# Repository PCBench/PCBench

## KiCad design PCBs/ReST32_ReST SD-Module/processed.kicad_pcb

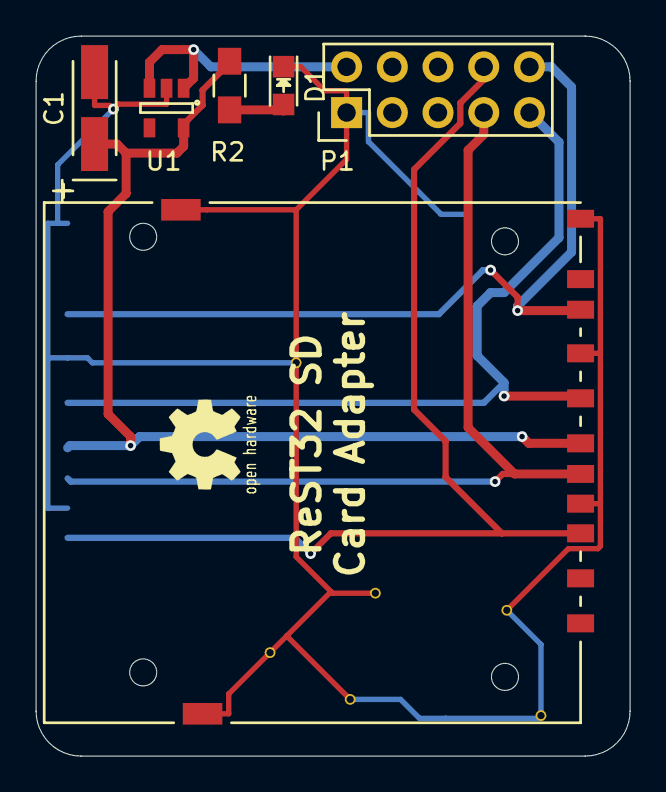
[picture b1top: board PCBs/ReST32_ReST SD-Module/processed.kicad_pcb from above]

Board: 2 copper layers, 33.0 x 40.0 mm, 7 parts (1 on the bottom side), 8 nets.

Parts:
C1: 2.2uF; TantalC_SizeA_EIA-3216_HandSoldering
CON1, CON2: uSD_Card; SD_Card_Receptacle
D1: Led_Small; LED_0805
P1: CONN_02X05; Pin_Header_Straight_2x05
R2: 1K; R_0805_HandSoldering
U1: MIC5205; SOT-23-5

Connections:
+3V3: C1.1, CON1.4, CON2.4, R2.1, U1.5
+5V: P1.2, U1.1, U1.3
/SPI-CS: CON1.2, CON2.2, P1.8
/SPI-MISO: CON1.7, CON2.7, P1.10
/SPI-MOSI: CON1.3, CON2.3, P1.7
/SPI-SCK: CON1.5, CON2.5, P1.9
GND: C1.2, CON1.6, CON1.10, CON1.11, CON1.12, CON1.13, CON2.6, CON2.10, CON2.11, CON2.12, CON2.13, D1.1, P1.1, U1.2
unnamed: D1.2, R2.2

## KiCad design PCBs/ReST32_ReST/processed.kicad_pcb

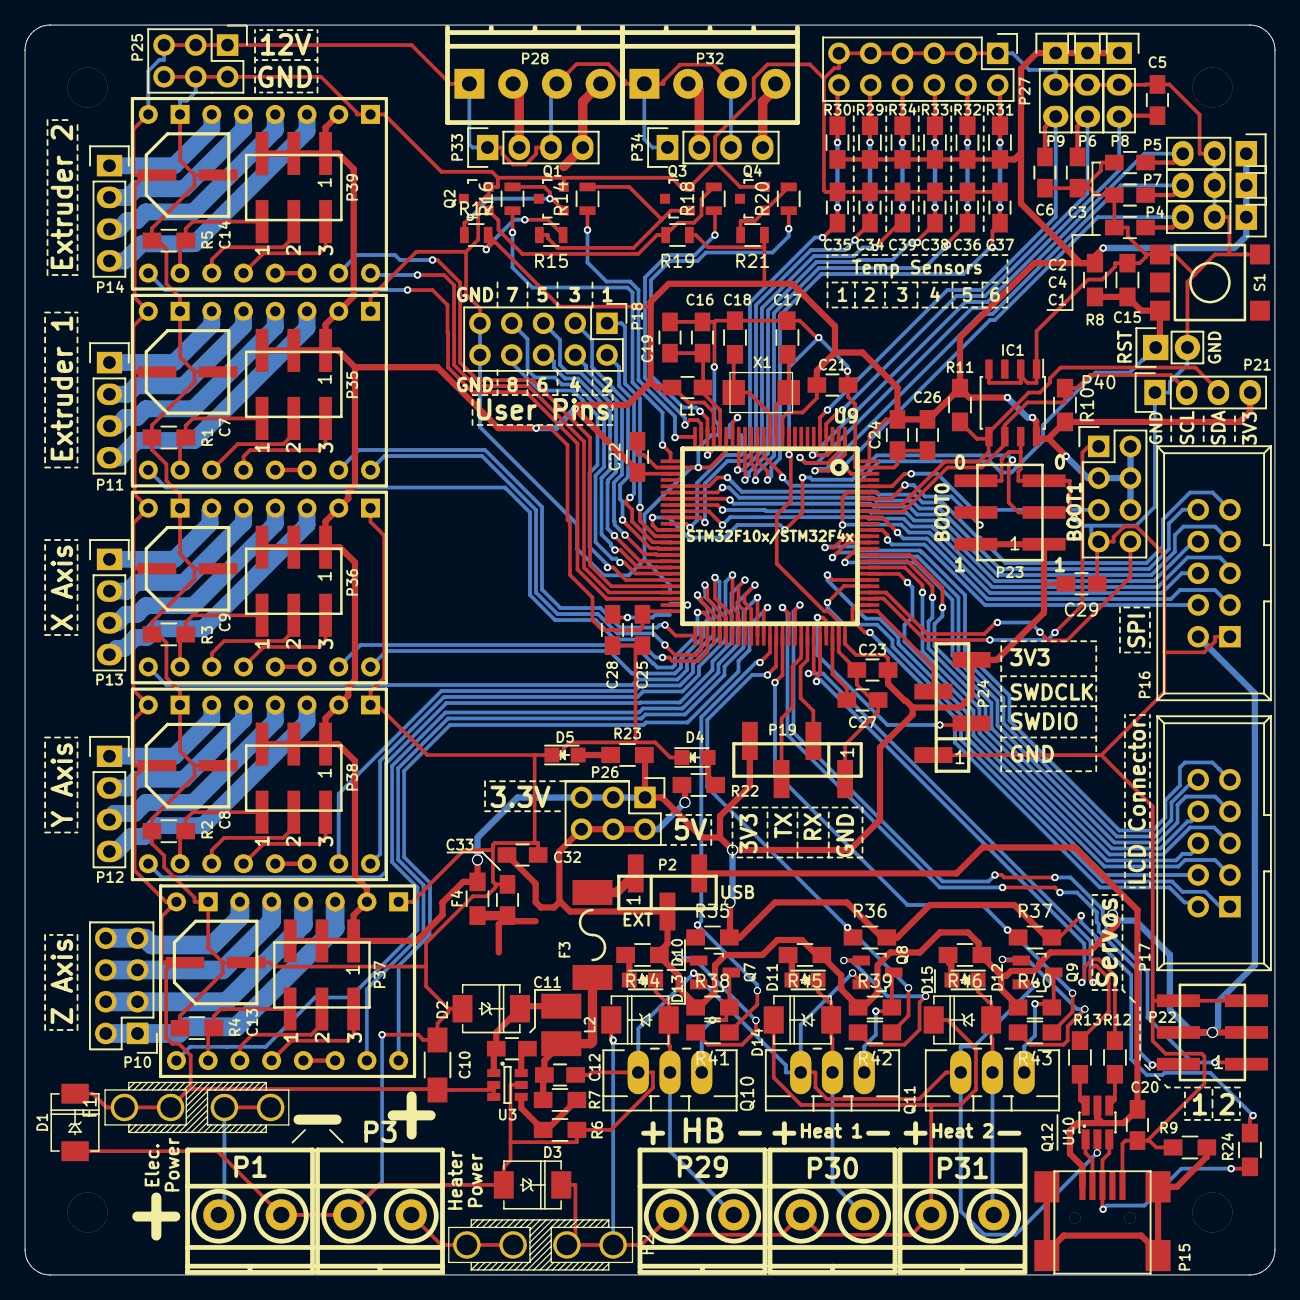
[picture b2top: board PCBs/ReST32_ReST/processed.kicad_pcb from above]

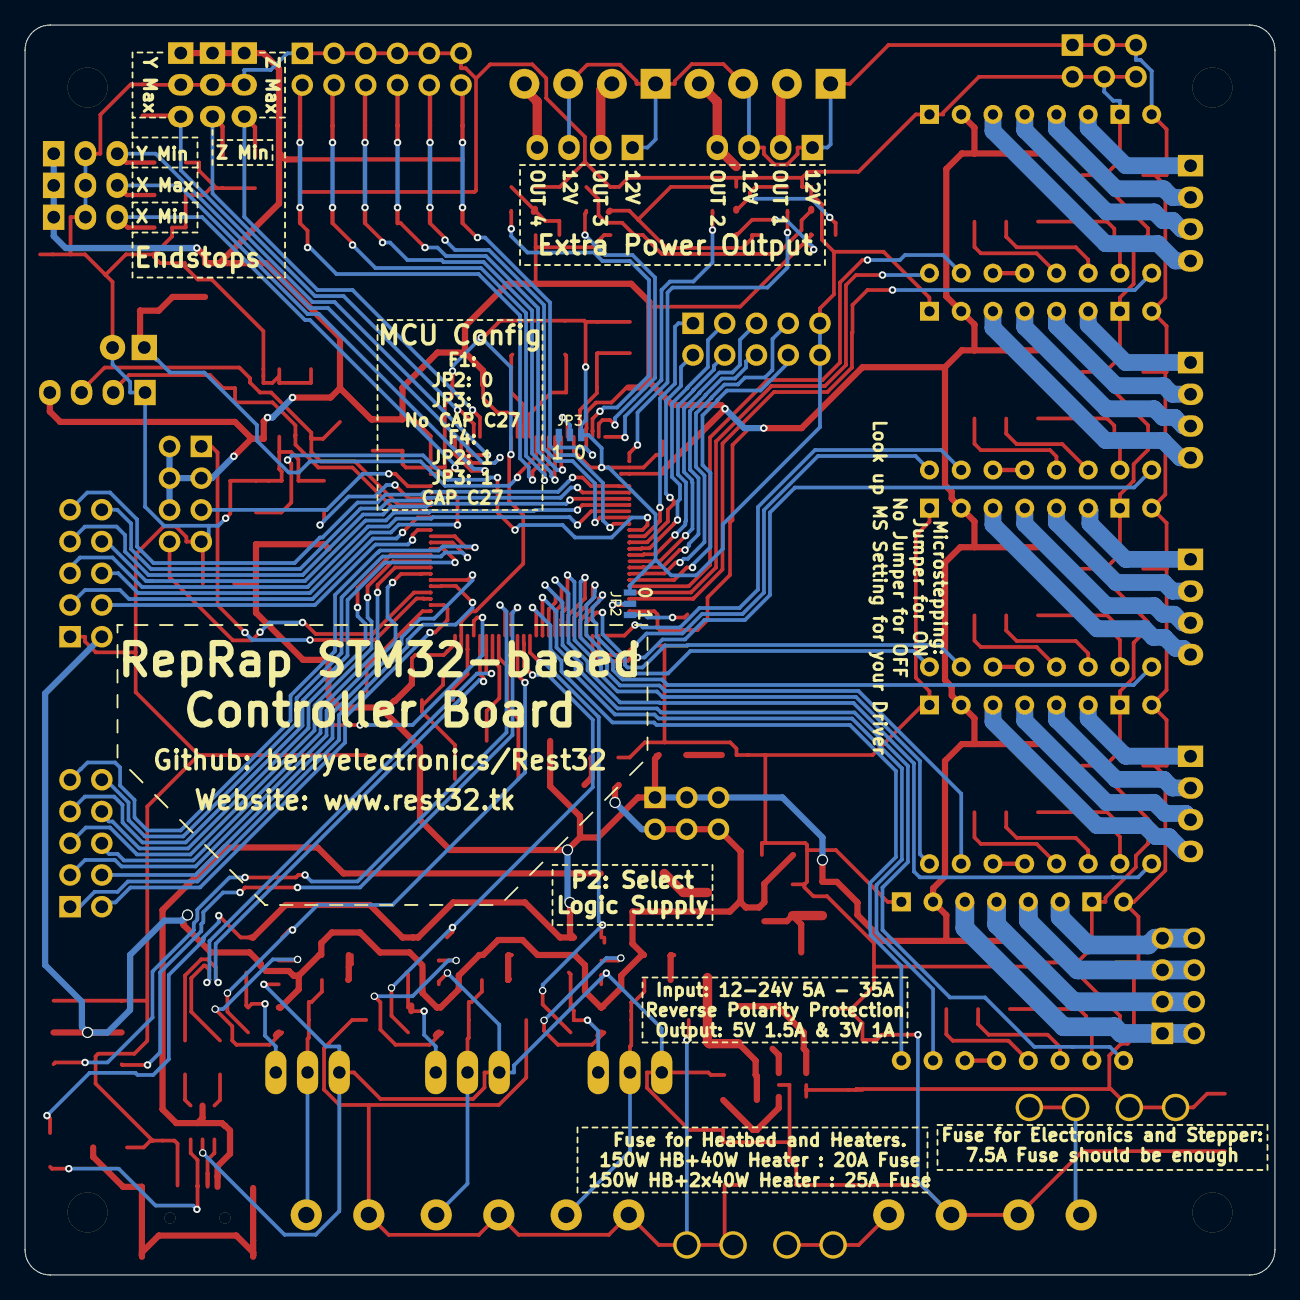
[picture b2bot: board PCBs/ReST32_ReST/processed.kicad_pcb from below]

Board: 2 copper layers, 100.0 x 100.0 mm, 159 parts (2 on the bottom side), 164 nets.

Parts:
C1, C2, C3, C4, C5, C6: 10nF; C_0805_HandSoldering
C7, C8, C9, C13, C14: 100uF; CP-PANASONIC-SMT_D8
C10: 10uF; C_1206_HandSoldering
C11: 22nF; C_0805_HandSoldering
C12, C26: 4.7uF; C_0805_HandSoldering
C15: 100nF; R_0805_HandSoldering
C16, C32, C33, C34, C35, C36, C37, C38, C39: 10uF; C_0805_HandSoldering
C17, C18: 10pF; R_0805_HandSoldering
C19, C20, C21, C22, C23, C24, C25, C29: 100nF; C_0805_HandSoldering
C27, C28: 2u2; C_0805_HandSoldering
D1, D3: 1N400x; DO-214AC.SMA
D2: B240A; DO-214AC.SMA
D4, D5, D10, D11, D12: LED; LED_0805
D13, D14, D15: D_1N400x-SMD; DO-214AC.SMA
F1, F2: F_Small; MINI-FUSE
F3: F_Small; FUSE-1812
F4: F_Small; R_0805_HandSoldering
IC1: AT24C256; SOIC-8_3.9x4.9mm_Pitch1.27mm
JP2, JP3: JUMPER3; S_JUMPER_3
L1: BEAD; C_0805_HandSoldering
L2: 4.7uH; CD32
P1, P3, P29, P30, P31: CONN_01X02; screw-5-2P
P2: CONN_01X03; bb02-hy03a
P4, P5, P6, P7, P8, P9: CONN_01X03; Pin_Header_Straight_1x03
P10, P40: CONN_02X04; Pin_Header_Straight_2x04
P11, P12, P13, P14, P21: CONN_01X04; Pin_Header_Straight_1x04
P15: USB_OTG; USB_Mini-B
P16, P17: CONN_02X05; IDC_Header_Straight_10pins
P18: CONN_02X05; Pin_Header_Straight_2x05
P19, P24: CONN_01X04; bb02-hy04a
P20: CONN_01X02; Pin_Header_Straight_1x02
P22, P23, P35, P36, P37, P38, P39: CONN_02X03; bb02-hp06
P25, P26: CONN_02X03; Pin_Header_Straight_2x03
P27: CONN_02X06; Pin_Header_Straight_2x06
P28, P32: CONN_02X02; pt_1,5-4-3,5-h
P33, P34: CONN_02X02; Pin_Header_Straight_1x04
Q1, Q2, Q3, Q4, Q7, Q8, Q9: BSS138; SOT-23
Q10, Q11, Q12: Q_AOT240L; TO-220_Neutral123_Vertical_LargePads
R1, R2, R3, R4, R5, R35, R36, R37, R38, R39, R40: 100K; R_0805_HandSoldering
R6: 28.7k; R_0805_HandSoldering
R7: 150K; R_0805_HandSoldering
R8: 10K; R_0805_HandSoldering
R9: 1M; R_0805_HandSoldering
R10, R11, R29, R30, R31, R32, R33, R34: 4K7; R_0805_HandSoldering
R12, R13, R41, R42, R43: 22R; R_0805_HandSoldering
R14, R16, R18, R20: 22R; R_0805
R15, R17, R19, R21: 100K; R_0805
R22, R23, R44, R45, R46: 1K; R_0805_HandSoldering
R24: 1K5; R_0805_HandSoldering
S1: SW_DIP_x2; SMD-BUTTON-6MM
U2, U5, U6, U7, U8: POLOLU_A4988; SWDIP8_.6W
U3: ACT4088; SOT-23-6
U9: STM32F10x/STM32F4x; LQFP100-14x14
U10: USBLC6-2; SOT32-6L
X1: Crystal_Small; 2P-5032

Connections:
+3V3: C21.1, C22.1, C23.1, C24.1, C25.1, C26.1, C29.2, F4.1, IC1.8, JP3.1, L1.1, P4.1, P5.1, P6.1, P7.1, P8.1, P9.1, P19.4, P21.4, P23.1, P23.2, P24.4, P26.1, P26.3, P26.5, P35.1, P35.3, P35.5, P36.1, P36.3, P36.5, P37.1, P37.3, P37.5, P38.1, P38.3, P38.5, P39.1, P39.3, P39.5, P40.2, P40.3, P40.4, P40.6, R8.2, R10.2, R11.2, R15.1, R17.2, R19.1, R21.1, R23.1, R24.2, R29.2, R30.2, R31.2, R32.2, R33.2, R34.2, R35.2, R36.2, R37.2, U2.2, U5.2, U6.2, U7.2, U8.2, U9.11, U9.22, U9.28, U9.50, U9.75, U9.100
+5V: C32.2, P2.2, P16.2, P22.3, P22.4, P26.2, P26.4, P26.6, R22.1, R38.1, R39.1, R40.1, R44.1, R45.1, R46.1
+12V: C7.1, C8.1, C9.1, C10.1, C13.1, C14.1, D1.1, F1.2, P25.1, P25.3, P25.5, P28.1, P28.3, P32.1, P32.3, P33.1, P33.3, P34.1, P34.3, U2.8, U3.2, U3.3, U5.8, U6.8, U7.8, U8.8
+12VA: D3.1, D13.1, D14.1, D15.1, F2.2, P29.1, P30.1, P31.1
/Extra Power Output/EXTRA_0_OUT: P28.2, P33.2
/Extra Power Output/EXTRA_1_OUT: P28.4, P33.4
/Extra Power Output/EXTRA_2_OUT: P32.2, P34.2
/Extra Power Output/EXTRA_3_OUT: P32.4, P34.4
/Heater/H0_GATE: Q7.1, R41.2
/Heater/H1_GATE: Q8.1, R42.2
/Heater/H2_GATE: Q9.1, R43.2
/Heater/HEATER_0_5VL: Q7.3, Q10.1, R38.2
/Heater/HEATER_0_OUT: D10.1, D13.2, P29.2, Q10.2
/Heater/HEATER_1_5VL: Q8.3, Q11.1, R39.2
/Heater/HEATER_1_OUT: D11.1, D14.2, P30.2, Q11.2
/Heater/HEATER_2_5VL: Q9.3, Q12.1, R40.2
/Heater/HEATER_2_OUT: D12.1, D15.2, P31.2, Q12.2
/Logic/USBP_D+: P15.3, R24.1, U10.3
/Logic/USBP_D-: P15.2, U10.1
/Logic/USBR+: R12.1, U10.4
/Logic/USBR-: R13.2, U10.6
/Power Input/12V-R: F1.1, P1.1
/Power Input/12VA-R: F2.1, P3.2
/Stepper and Endstop/E0M1: P35.6, R1.1, U2.10
/Stepper and Endstop/E0M2: P35.4, U2.11
/Stepper and Endstop/E0M3: P35.2, U2.12
/Stepper and Endstop/E0_1A: P11.3, U2.4
/Stepper and Endstop/E0_1B: P11.4, U2.3
/Stepper and Endstop/E0_2A: P11.2, U2.5
/Stepper and Endstop/E0_2B: P11.1, U2.6
/Stepper and Endstop/E1M1: P39.6, R5.1, U8.10
/Stepper and Endstop/E1M2: P39.4, U8.11
/Stepper and Endstop/E1M3: P39.2, U8.12
/Stepper and Endstop/E1_1A: P14.3, U8.4
/Stepper and Endstop/E1_1B: P14.4, U8.3
/Stepper and Endstop/E1_2A: P14.2, U8.5
/Stepper and Endstop/E1_2B: P14.1, U8.6
/Stepper and Endstop/XM1: P36.6, R3.1, U6.10
/Stepper and Endstop/XM2: P36.4, U6.11
/Stepper and Endstop/XM3: P36.2, U6.12
/Stepper and Endstop/X_1A: P13.3, U6.4
/Stepper and Endstop/X_1B: P13.4, U6.3
/Stepper and Endstop/X_2A: P13.2, U6.5
/Stepper and Endstop/X_2B: P13.1, U6.6
/Stepper and Endstop/YM1: P38.6, R2.1, U5.10
/Stepper and Endstop/YM2: P38.4, U5.11
/Stepper and Endstop/YM3: P38.2, U5.12
/Stepper and Endstop/Y_1A: P12.3, U5.4
/Stepper and Endstop/Y_1B: P12.4, U5.3
/Stepper and Endstop/Y_2A: P12.2, U5.5
/Stepper and Endstop/Y_2B: P12.1, U5.6
/Stepper and Endstop/ZM1: P37.6, R4.1, U7.10
/Stepper and Endstop/ZM2: P37.4, U7.11
/Stepper and Endstop/ZM3: P37.2, U7.12
/Stepper and Endstop/Z_1A: P10.3, P10.4, U7.4
/Stepper and Endstop/Z_1B: P10.1, P10.2, U7.3
/Stepper and Endstop/Z_2A: P10.5, P10.6, U7.5
/Stepper and Endstop/Z_2B: P10.7, P10.8, U7.6
BOOT_0: P23.4, U9.94
BOOT_1: P23.3, U9.37
DISPLAY_CD: P17.2, U9.77
DISPLAY_CS: P17.1, U9.80
DISPLAY_D0: P17.4, U9.81
DISPLAY_D1: P17.3, U9.82
DISPLAY_D2: P17.6, U9.83
DISPLAY_D3: P17.5, U9.84
DISPLAY_D4: P17.8, U9.85
DISPLAY_D5: P17.7, U9.86
DISPLAY_D6: P17.10, U9.87
DISPLAY_D7: P17.9, U9.88
DISPLAY_EXTRA_0: P16.6, U9.95
DISPLAY_EXTRA_1: P40.5, U9.96
DISPLAY_RD: P16.3, U9.91
DISPLAY_WR: P16.4, U9.89
ENDSTOP_X_MAX: C4.1, P7.3, U9.1
ENDSTOP_X_MIN: C1.1, P4.3, U9.98
ENDSTOP_Y_MAX: C5.1, P8.3, U9.3
ENDSTOP_Y_MIN: C2.1, P5.3, U9.2
ENDSTOP_Z_MAX: C6.1, P9.3, U9.5
ENDSTOP_Z_MIN: C3.1, P6.3, U9.4
EXTRA_0: R16.1, U9.26
EXTRA_1: R14.1, U9.25
EXTRA_2: R18.1, U9.24
EXTRA_3: R20.1, U9.23
GND: C1.2, C2.2, C3.2, C4.2, C5.2, C6.2, C7.2, C8.2, C9.2, C10.2, C12.2, C13.2, C14.2, C15.1, C16.2, C17.1, C18.2, C19.2, C20.2, C21.2, C22.2, C23.2, C24.2, C25.2, C26.2, C27.2, C28.2, C29.1, C32.1, C33.2, C34.2, C35.2, C36.2, C37.2, C38.2, C39.2, D1.2, D2.2, D3.2, D4.1, D5.1, IC1.1, IC1.2, IC1.4, IC1.7, JP2.3, JP3.3, P1.2, P3.1, P4.2, P5.2, P6.2, P7.2, P8.2, P9.2, P15.5, P16.1, P18.9, P18.10, P19.1, P20.2, P21.1, P22.5, P22.6, P23.5, P23.6, P24.1, P25.2, P25.4, P25.6, P27.1, P27.3, P27.5, P27.7, P27.9, P27.11, P40.7, Q1.2, Q2.2, Q3.2, Q4.2, Q7.2, Q8.2, Q9.2, Q10.3, Q11.3, Q12.3, R1.2, R2.2, R3.2, R4.2, R5.2, R6.1, R9.1, S1.3, S1.4, U2.1, U2.7, U3.5, U5.1, U5.7, U6.1, U6.7, U7.1, U7.7, U8.1, U8.7, U9.10, U9.20, U9.27, U9.74, U9.99, U10.2
HEATER_0: R35.1, R41.1, U9.63
HEATER_1: R36.1, R42.1, U9.64
HEATER_2: R37.1, R43.1, U9.65
I2C_SCL: IC1.6, P21.2, R10.1, U9.92
I2C_SDA: IC1.5, P21.3, R11.1, U9.93
unnamed: C11.1, D2.1, L2.1, U3.1
unnamed: C11.2, U3.6
unnamed: C12.1, F3.2, L2.2, R7.2
unnamed: C16.1, C19.1, L1.2, U9.21
unnamed: C17.2, U9.12, X1.2
unnamed: C18.1, U9.13, X1.1
unnamed: C28.1, JP2.1
unnamed: C33.1, F4.2
unnamed: D4.2, R22.2
unnamed: D5.2, R23.2
unnamed: D10.2, R44.2
unnamed: D11.2, R45.2
unnamed: D12.2, R46.2
unnamed: P15.6, R9.2
unnamed: Q1.1, R16.2, R17.1
unnamed: Q2.1, R18.2, R19.2
unnamed: Q3.1, R14.2, R15.2
unnamed: Q4.1, R20.2, R21.2
unnamed: R6.2, R7.1, U3.4
unnamed: U2.13, U2.14
unnamed: U5.13, U5.14
unnamed: U6.13, U6.14
unnamed: U7.13, U7.14
unnamed: U8.13, U8.14
P_VCAP_1: JP2.2, U9.49
P_VCAP_2: C27.1, U9.73
P_VSSA: JP3.2, U9.19
RESET: C15.2, P20.1, R8.1, S1.2, U9.14
SERVO_0: P22.2, U9.66
SERVO_1: P22.1, U9.67
SPI_CS1: P16.8, U9.33
SPI_CS2: P16.5, U9.34
SPI_MISO: P16.10, U9.31
SPI_MOSI: P16.7, U9.32
SPI_SCK: P16.9, U9.30
STEPPER_E_0_DIR: U2.16, U9.52
STEPPER_E_0_EN: U2.9, U9.53
STEPPER_E_0_STEP: U2.15, U9.51
STEPPER_E_1_DIR: U8.16, U9.47
STEPPER_E_1_EN: U8.9, U9.48
STEPPER_E_1_STEP: U8.15, U9.46
STEPPER_X_DIR: U6.16, U9.55
STEPPER_X_EN: U6.9, U9.56
STEPPER_X_STEP: U6.15, U9.54
STEPPER_Y_DIR: U5.16, U9.58
STEPPER_Y_EN: U5.9, U9.59
STEPPER_Y_STEP: U5.15, U9.57
STEPPER_Z_DIR: U7.16, U9.62
STEPPER_Z_EN: U7.9, U9.60
STEPPER_Z_STEP: U7.15, U9.61
SWD_CLK: P24.3, U9.76
SWD_IO: P24.2, U9.72
TEMP_0: C37.1, P27.2, R31.1, U9.15
TEMP_1: C36.1, P27.4, R32.1, U9.16
TEMP_2: C38.1, P27.6, R33.1, U9.17
TEMP_3: C39.1, P27.8, R34.1, U9.18
TEMP_4: C34.1, P27.10, R29.1, U9.35
TEMP_5: C35.1, P27.12, R30.1, U9.36
UART_1_RX: P19.2, U9.69
UART_1_TX: P19.3, U9.68
UART_4_RX: P40.8, U9.79
UART_4_TX: P40.1, U9.78
USB_MCU+: R12.2, U9.71
USB_MCU-: R13.1, U9.70
USER_0: P18.1, U9.38
USER_1: P18.2, U9.39
USER_2: P18.3, U9.40
USER_3: P18.4, U9.41
USER_4: P18.5, U9.42
USER_5: P18.6, U9.43
USER_6: P18.7, U9.44
USER_7: P18.8, U9.45
VCC: C20.1, P2.3, P15.1, U10.5
VEE: F3.1, P2.1

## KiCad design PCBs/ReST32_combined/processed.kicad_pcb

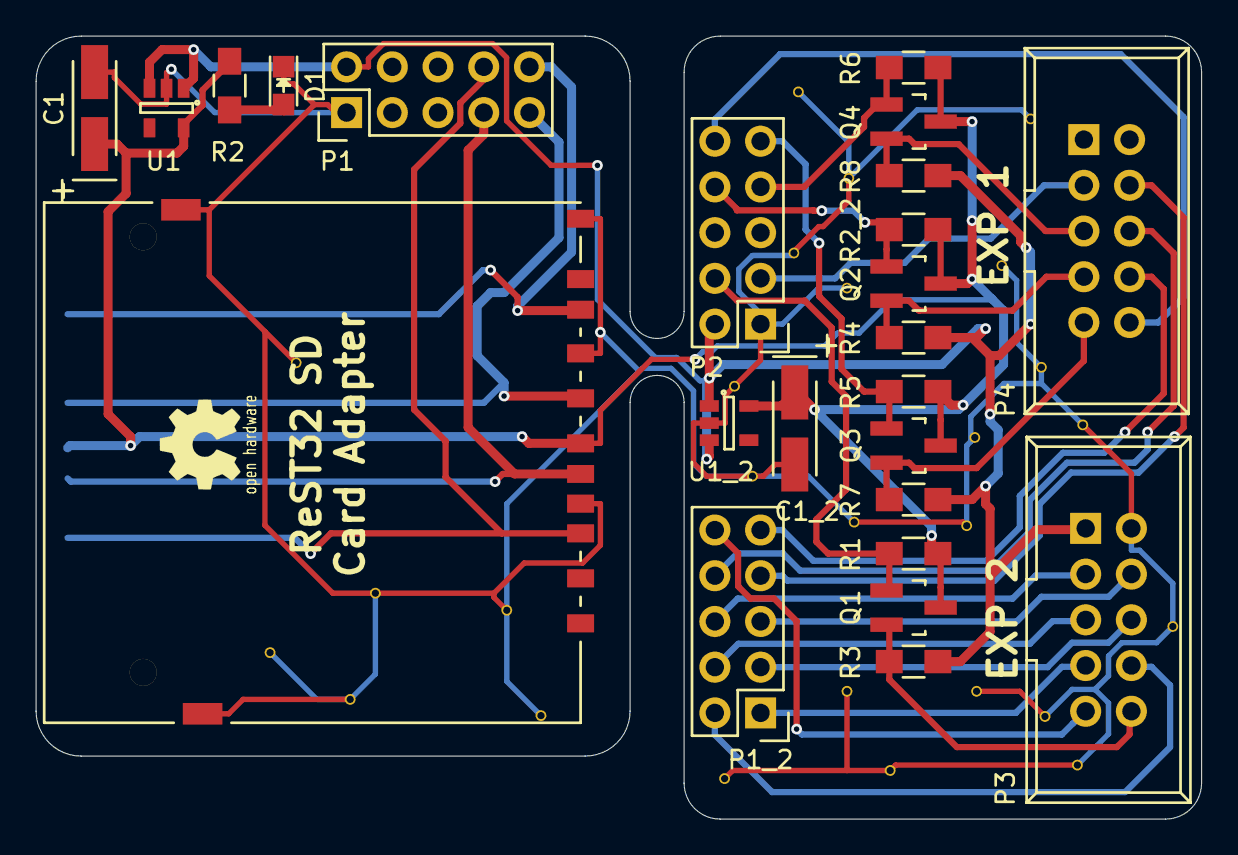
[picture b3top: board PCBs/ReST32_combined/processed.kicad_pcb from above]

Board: 2 copper layers, 64.8 x 43.5 mm, 24 parts (0 on the bottom side), 28 nets.

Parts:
C1: CP1_Small; TantalC_SizeA_EIA-3216_HandSoldering
C1_2: 2.2uF; TantalC_SizeA_EIA-3216_HandSoldering
CON1: uSD_Card; SD_Card_Receptacle
D1: Led_Small; LED_0805
P1, P1_2, P2: CONN_02X05; Pin_Header_Straight_2x05
P3, P4: CONN_02X05; IDC_Header_Straight_10pins
Q1, Q2, Q3, Q4: BSS138; SOT-23_Handsoldering
R1, R2_2, R3, R4, R5, R6, R7, R8: 10K; R_0805_HandSoldering
R2: 1K; R_0805_HandSoldering
U1, U1_2: MIC5205; SOT-23-5

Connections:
+3V3: C1.1, C1_2.1, CON1.4, Q1.3, Q2.3, Q3.3, Q4.3, R1.1, R2.1, R2_2.1, R5.1, R6.1, U1.5, U1_2.5
+5V: P1.2, P2.2, P3.1, R3.1, R4.1, R7.1, R8.1, U1.1, U1.3, U1_2.1, U1_2.3
/BEEP: P3.10, Q1.2, R3.2
/CS: P4.7, Q2.2, R4.2
/DISPLAY_CD: P1_2.2, P3.8
/DISPLAY_CS: P1_2.1, P3.7
/DISPLAY_D0: P1_2.4, P3.5
/DISPLAY_D1: P1_2.3, P3.6
/DISPLAY_D2: P1_2.6, P3.3
/DISPLAY_D3: P1_2.5, P3.4
/DISPLAY_D4: P1_2.8, P4.6
/DISPLAY_D5: P1_2.7, P4.4
/DISPLAY_D6: P1_2.10, P3.9
/DISPLAY_D7: P1_2.9, P4.8
/DISPLAY_RD: P2.3, P4.3
/DISPLAY_WR: P2.4, Q1.1, R1.2
/MISO: P2.10, P4.10
/MOSI: P4.5, Q4.2, R8.2
/SCK: P4.9, Q3.2, R7.2
/SPI-CS: CON1.2, P1.8
/SPI-MISO: CON1.7, P1.10
/SPI-MOSI: CON1.3, P1.7
/SPI-SCK: CON1.5, P1.9
/SPI_CS1: P2.8, Q2.1, R2_2.2
/SPI_MOSI: P2.7, Q4.1, R6.2
/SPI_SCK: P2.9, Q3.1, R5.2
GND: C1.2, C1_2.2, CON1.6, CON1.10, CON1.11, CON1.12, CON1.13, D1.1, P1.1, P2.1, P3.2, U1.2, U1_2.2
unnamed: D1.2, R2.2

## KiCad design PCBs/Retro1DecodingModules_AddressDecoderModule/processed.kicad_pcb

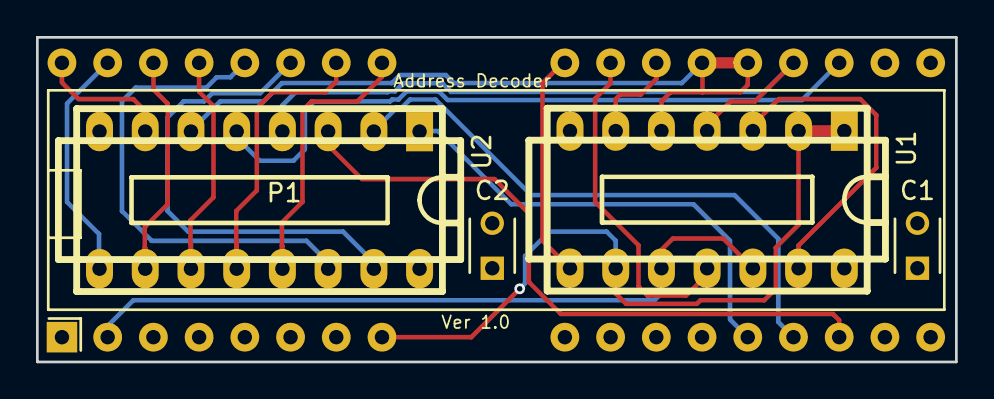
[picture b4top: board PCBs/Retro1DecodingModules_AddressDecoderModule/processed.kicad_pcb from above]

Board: 4 copper layers, 51.1 x 18.0 mm, 5 parts (0 on the bottom side), 22 nets.

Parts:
C1, C2: .1uf; C_Disc_D3_P2.5
P1: CONN_02X20_DIP40; decoder_footprint
U1: 74LS00; dil_14-300_socket
U2: 74LS138N; dil_16-300_socket

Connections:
A8: P1.16, U2.1
A9: P1.17, U2.2
A10: P1.18, U2.3
A13: P1.23, U2.5
A14: P1.24, U1.4, U2.4
A15: P1.25, P1.26, U1.5, U2.6
CS7: P1.39, U2.9
CS8: P1.40, U2.7
CS_ACIA1: P1.33, U2.13
CS_ACIA2: P1.34, U2.12
CS_RTC: P1.38, U2.10
CS_SID: P1.37, U2.11
CS_VIA1: P1.35, U2.15
CS_VIA2: P1.36, U2.14
GND: C1.1, C2.2, P1.20, U1.7, U2.8
unnamed: U1.3, U1.13
OE: P1.29, U1.8
PHI2: P1.2, U1.10, U1.12
ROM_CE: P1.27, U1.6
RW: P1.8, U1.1, U1.2, U1.9
VCC: C1.2, C2.1, P1.1, P1.21, U1.14, U2.16
WE: P1.28, U1.11

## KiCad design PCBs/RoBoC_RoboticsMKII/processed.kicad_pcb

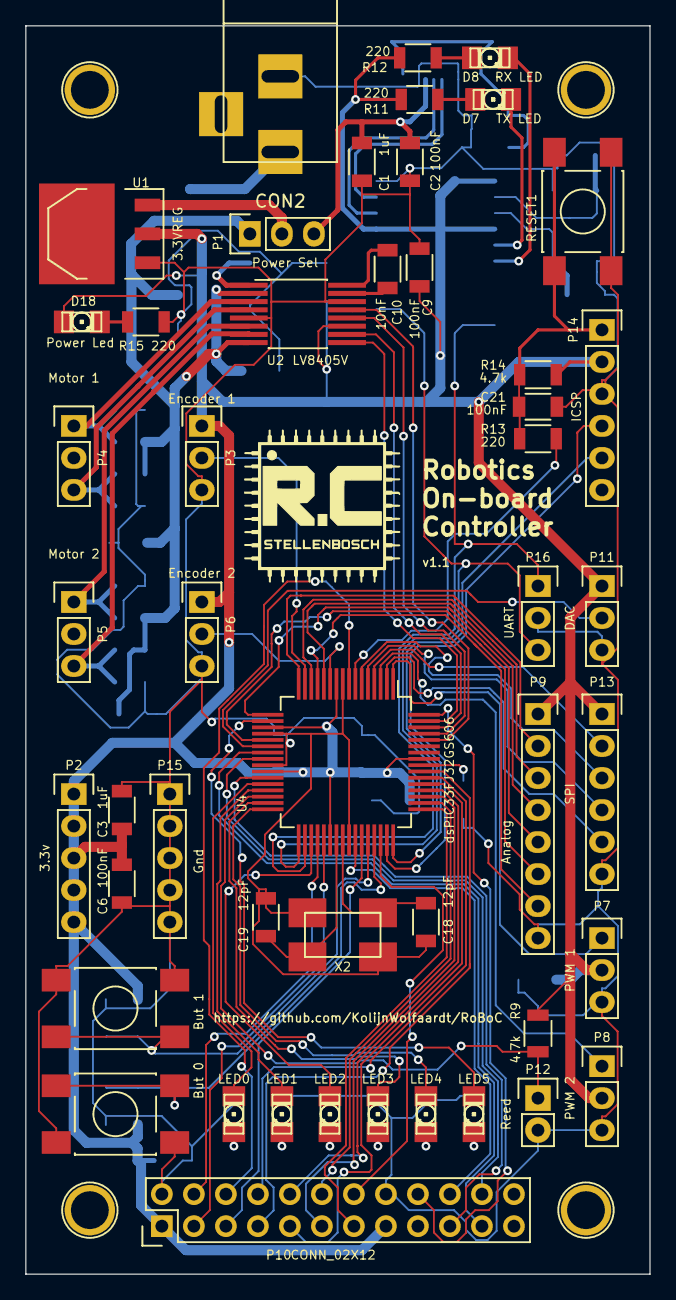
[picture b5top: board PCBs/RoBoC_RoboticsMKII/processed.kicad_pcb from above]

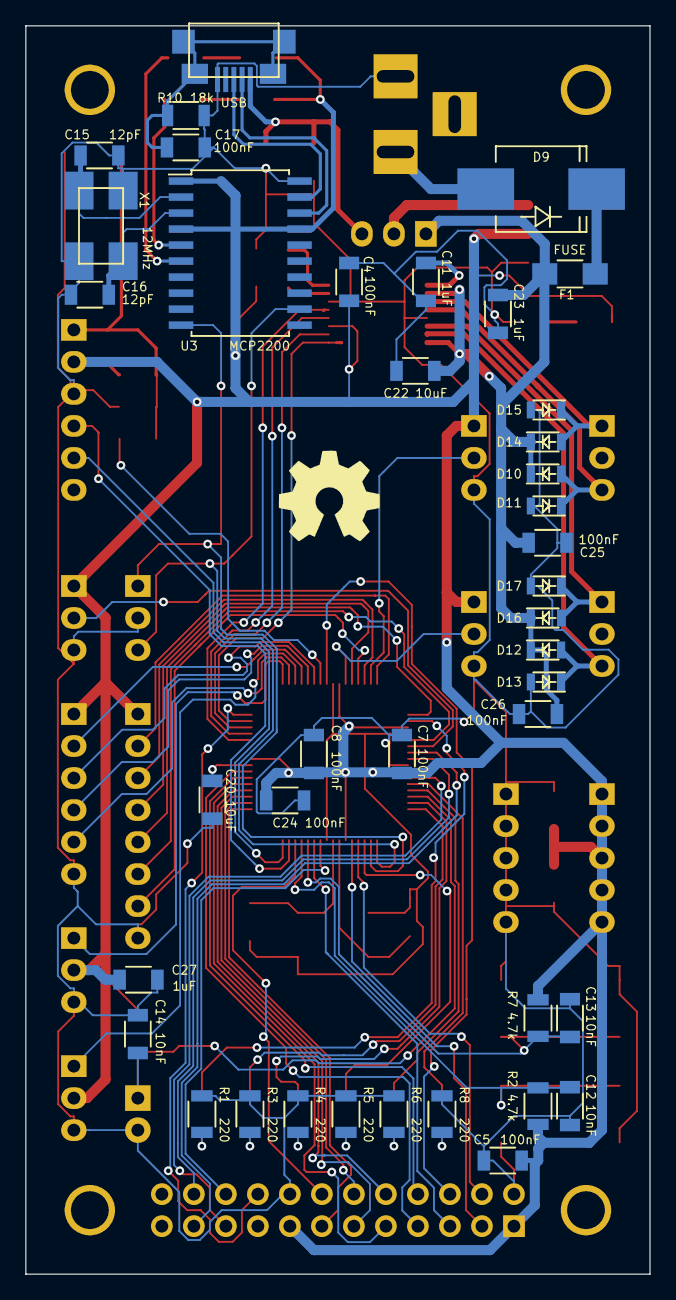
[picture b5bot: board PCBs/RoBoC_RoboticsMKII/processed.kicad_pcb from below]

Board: 2 copper layers, 49.5 x 99.1 mm, 92 parts (40 on the bottom side), 84 nets.

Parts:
C1, C3, C4, C23, C27: 1uF; C_1206
C2, C5, C6, C7, C8, C9, C11, C17, C21, C24, C25, C26: 100nF; C_1206
C10, C12, C13, C14: 10nF; C_1206
C15, C16, C18, C19: 12pF; C_1206
C20, C22: 10uF; C_1206
CON1: USB; USB_Micro
CON2: BARREL_JACK
D1: LED5; LED-1206
D2: LED4; LED-1206
D3: LED3; LED-1206
D4: LED2; LED-1206
D5: LED1; LED-1206
D6: LED0; LED-1206
D7: TX LED; LED-1206
D8: RX LED; LED-1206
D9: D; Diode-SMC_Handsoldering
D10, D11, D12, D13, D14, D15, D16, D17: D; SOD-323
D18: Power Led; LED-1206
F1: FUSE; R_1206_HandSoldering
P1: Power Sel; Pin_Header_Straight_1x03
P2: 3.3v; Pin_Header_Straight_1x05
P3: Encoder 1; Pin_Header_Straight_1x03
P4: Motor 1; Pin_Header_Straight_1x03
P5: Motor 2; Pin_Header_Straight_1x03
P6: Encoder 2; Pin_Header_Straight_1x03
P7: PWM 1; Pin_Header_Straight_1x03
P8: PWM 2; Pin_Header_Straight_1x03
P9: Analog; Pin_Header_Straight_1x08
P10: CONN_02X12; Pin_Header_Straight_2x12
P11: DAC; Pin_Header_Straight_1x03
P12: Reed; Pin_Header_Straight_1x02
P13: SPI; Pin_Header_Straight_1x06
P14: ICSP; Pin_Header_Straight_1x06
P15: Gnd; Pin_Header_Straight_1x05
P16: UART; Pin_Header_Straight_1x03
P96, P97, P98, P99: CONN_01X01; MountingHole3mm
R1, R3, R4, R5, R6, R8, R11, R12, R13, R15: 220; R_1206
R2, R7, R9, R14: 4.7k; R_1206
R10: 18k; R_1206
RESET1: DPST; SW_SPST_bigpads
SW0: But 0; SW_SPST_bigpads
SW1: But 1; SW_SPST_bigpads
U1: 3.3VREG; SOT-223
U2: LV8405V; SSOP-16_4.4x5.2mm_Pitch0.65mm_Handsoldering
U3: MCP2200; SOIC-20_7.5x12.8mm_Pitch1.27mm
U4: dsPIC33FJ32GS606; TQFP-64_10x10mm_Pitch0.5mm_handsoldering
X1: 12MHz; Crystal 6x 3.5 x 1.1mm
X2: 10MHz; Crystal 6x 3.5 x 1.1mm

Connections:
/gpio/AN0: P9.2, U4.16
/gpio/AN1: P9.3, U4.14
/gpio/AN2: P9.4, U4.12
/gpio/AN3: P9.5, U4.17
/gpio/AN4: P9.6, U4.21
/gpio/AN5: P9.7, U4.13
/gpio/BUT_0: C12.2, R2.2, SW0.1, U4.45
/gpio/BUT_1: C13.2, R7.2, SW1.1, U4.44
/gpio/DACOUT: P11.2, U4.22
/gpio/DATA_0: P10.14, U4.46
/gpio/DATA_1: P10.13, U4.49
/gpio/DATA_2: P10.12, U4.50
/gpio/DATA_3: P10.11, U4.51
/gpio/DATA_4: P10.10, U4.52
/gpio/DATA_5: P10.9, U4.53
/gpio/DATA_6: P10.8, U4.54
/gpio/DATA_7: P10.7, U4.55
/gpio/Href: P10.6, U4.8
/gpio/LED0: D6.1, U4.28
/gpio/LED1: D5.1, U4.29
/gpio/LED2: D4.1, U4.35
/gpio/LED3: D3.1, U4.31
/gpio/LED4: D2.1, U4.32
/gpio/LED5: D1.1, U4.18
/gpio/RCK: P10.18, U4.64
/gpio/Reed: C14.2, P12.1, R9.2, U4.30
/gpio/SIO_C: P10.3, U4.37
/gpio/SIO_D: P10.4, U4.36
/gpio/SPI_CLK: P13.2, U4.4
/gpio/SPI_MISO: P13.4, U4.5
/gpio/SPI_MOSI: P13.3, U4.6
/gpio/SPI_SS: P13.5, U4.2
/gpio/vSync: P10.5, U4.43
/gpio/~OE: P10.20, U4.42
/gpio/~RRST: P10.22, U4.24
/gpio/~WR: P10.19, U4.27
/gpio/~WRST: P10.21, U4.23
/mcu/MCLR: R13.2, U4.7
/mcu/MCLR_in: C21.1, P14.1, R13.1, R14.1, RESET1.1
/mcu/MOT1_D1: U2.13, U4.60
/mcu/MOT1_D2: U2.12, U4.61
/mcu/MOT1_ENC: P3.2, U4.15
/mcu/MOT2_D1: U2.10, U4.62
/mcu/MOT2_D2: U2.9, U4.63
/mcu/MOT2_ENC: P6.2, U4.11
/mcu/OSC1: C18.2, U4.40, X2.1
/mcu/OSC2: C19.2, U4.39, X2.2
/mcu/PGC: P14.5, U4.48
/mcu/PGD: P14.4, U4.47
/mcu/Vcap: C20.2, U4.56
/motors/C1H: C10.1, U2.16
/motors/C1L: C10.2, U2.15
/motors/MOT1_1: D14.1, D15.2, P4.1, U2.3
/motors/MOT1_2: D10.1, D11.2, P4.3, U2.4
/motors/MOT2_1: D16.1, D17.2, P5.1, U2.6
/motors/MOT2_2: D12.1, D13.2, P5.3, U2.7
/motors/PWM1: P7.1, U4.1
/motors/PWM2: P8.1, U4.3
/motors/VG: C11.1, U2.1
/motors/V_Bat: C22.1, C23.1, C25.1, C26.1, D10.2, D12.2, D14.2, D16.2, F1.2, P1.1, U2.2, U2.8
/power/V_USB: C1.1, C2.1, CON1.1, P1.3
/usb/MCU_RX: P16.1, U3.10, U4.34
/usb/MCU_TX: P16.3, U3.12, U4.33
/usb/RX_LED: D8.2, U3.6
/usb/TX_LED: D7.2, U3.5
/usb/USB_D+: CON1.3, U3.19
/usb/USB_D-: CON1.2, U3.18
/usb/USB_OSC1: C15.1, U3.2, X1.1
/usb/USB_OSC2: C16.1, U3.3, X1.2
GND: C1.2, C2.2, C3.2, C4.2, C5.2, C6.2, C7.2, C8.2, C9.2, C11.2, C12.1, C13.1, C14.1, C15.2, C16.2, C17.2, C18.1, C19.1, C20.1, C21.2, C22.2, C23.2, C24.2, C25.2, C26.2, C27.2, CON1.5, CON2.2, D11.1, D13.1, D15.1, D17.1, P3.3, P6.3, P7.3, P8.3, P9.8, P10.2, P10.16, P11.3, P12.2, P13.6, P14.3, P15.1, P15.2, P15.3, P15.4, P15.5, P16.2, R1.2, R3.2, R4.2, R5.2, R6.2, R8.2, R10.2, R15.2, RESET1.2, SW0.2, SW1.2, U1.1, U2.5, U2.14, U3.20, U4.9, U4.20, U4.25, U4.41, X1.3, X2.3
unnamed: C17.1, CON1.6, CON1.7, CON1.8, CON1.9, R10.1
unnamed: CON2.1, D9.1
unnamed: D1.2, R1.1
unnamed: D2.2, R3.1
unnamed: D3.2, R4.1
unnamed: D4.2, R5.1
unnamed: D5.2, R6.1
unnamed: D6.2, R8.1
unnamed: D7.1, R11.2
unnamed: D8.1, R12.2
unnamed: D9.2, F1.1
unnamed: D18.2, R15.1
unnamed: P1.2, U1.3
V3.3: C3.1, C4.1, C5.1, C6.1, C7.1, C8.1, C9.1, C24.1, C27.1, D18.1, P2.1, P2.2, P2.3, P2.4, P2.5, P3.1, P6.1, P7.2, P8.2, P9.1, P10.1, P10.15, P11.1, P13.1, P14.2, R2.1, R7.1, R9.1, R11.1, R12.1, R14.2, U1.2, U2.11, U3.1, U3.4, U3.17, U4.10, U4.19, U4.26, U4.38, U4.57

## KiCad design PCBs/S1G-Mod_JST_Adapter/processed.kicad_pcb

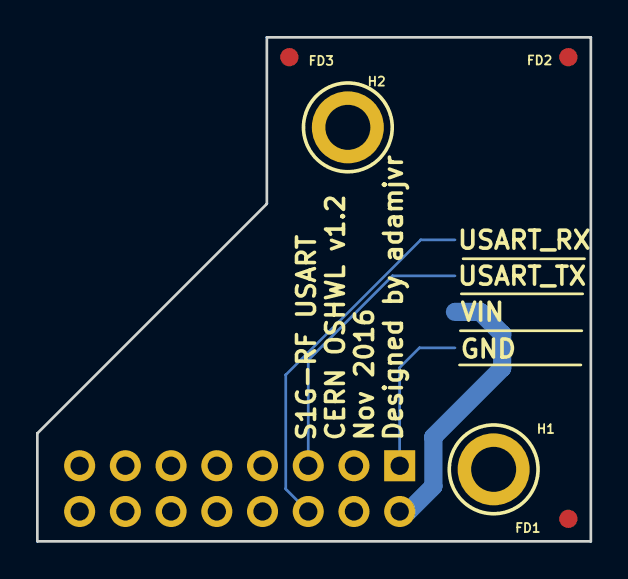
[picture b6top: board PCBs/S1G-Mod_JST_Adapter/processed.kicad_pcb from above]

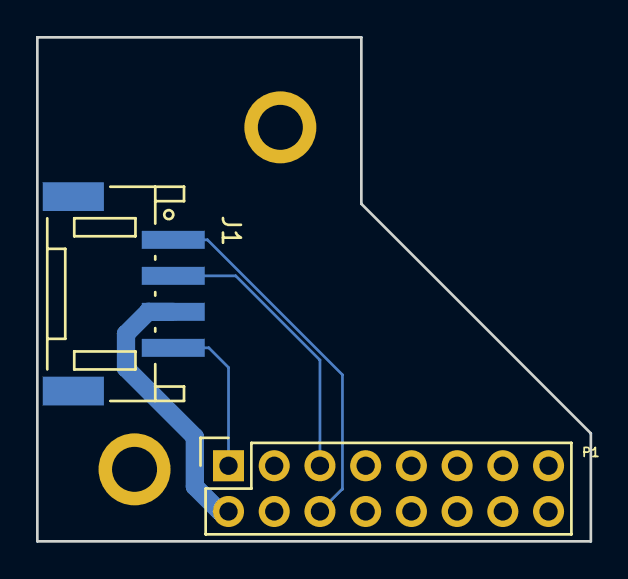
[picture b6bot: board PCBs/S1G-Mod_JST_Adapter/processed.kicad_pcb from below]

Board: 2 copper layers, 30.8 x 28.0 mm, 7 parts (2 on the bottom side), 4 nets.

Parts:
FD1, FD2, FD3: FIDUCIAL
H1, H2: M2.5_Hole; M2.5_HOLE
J1: S4B-PH-SM4-TB(LF)(SN)
P1: CONN_02X08; Socket_Strip_Straight_2x08

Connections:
/USART1_RX: J1.1, P1.6
/USART1_TX: J1.2, P1.5
/VIN: J1.3, P1.2
GND: J1.4, P1.1
